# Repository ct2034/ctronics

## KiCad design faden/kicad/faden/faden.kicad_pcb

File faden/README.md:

Pedal properties
----------------

* based on  [General Guitar Gadgets](http://www.generalguitargadgets.com/how-to-build-it/technical-help/articles/design-distortion/) ([pdf](/faden/DesignYourOwnDistortion_GeneralGuitarGadgets.pdf))
* tweaks:
  * For low tunings (C2 - 65,4Hz lowest note) 
  * BigMuff-style tone control (see pdf)

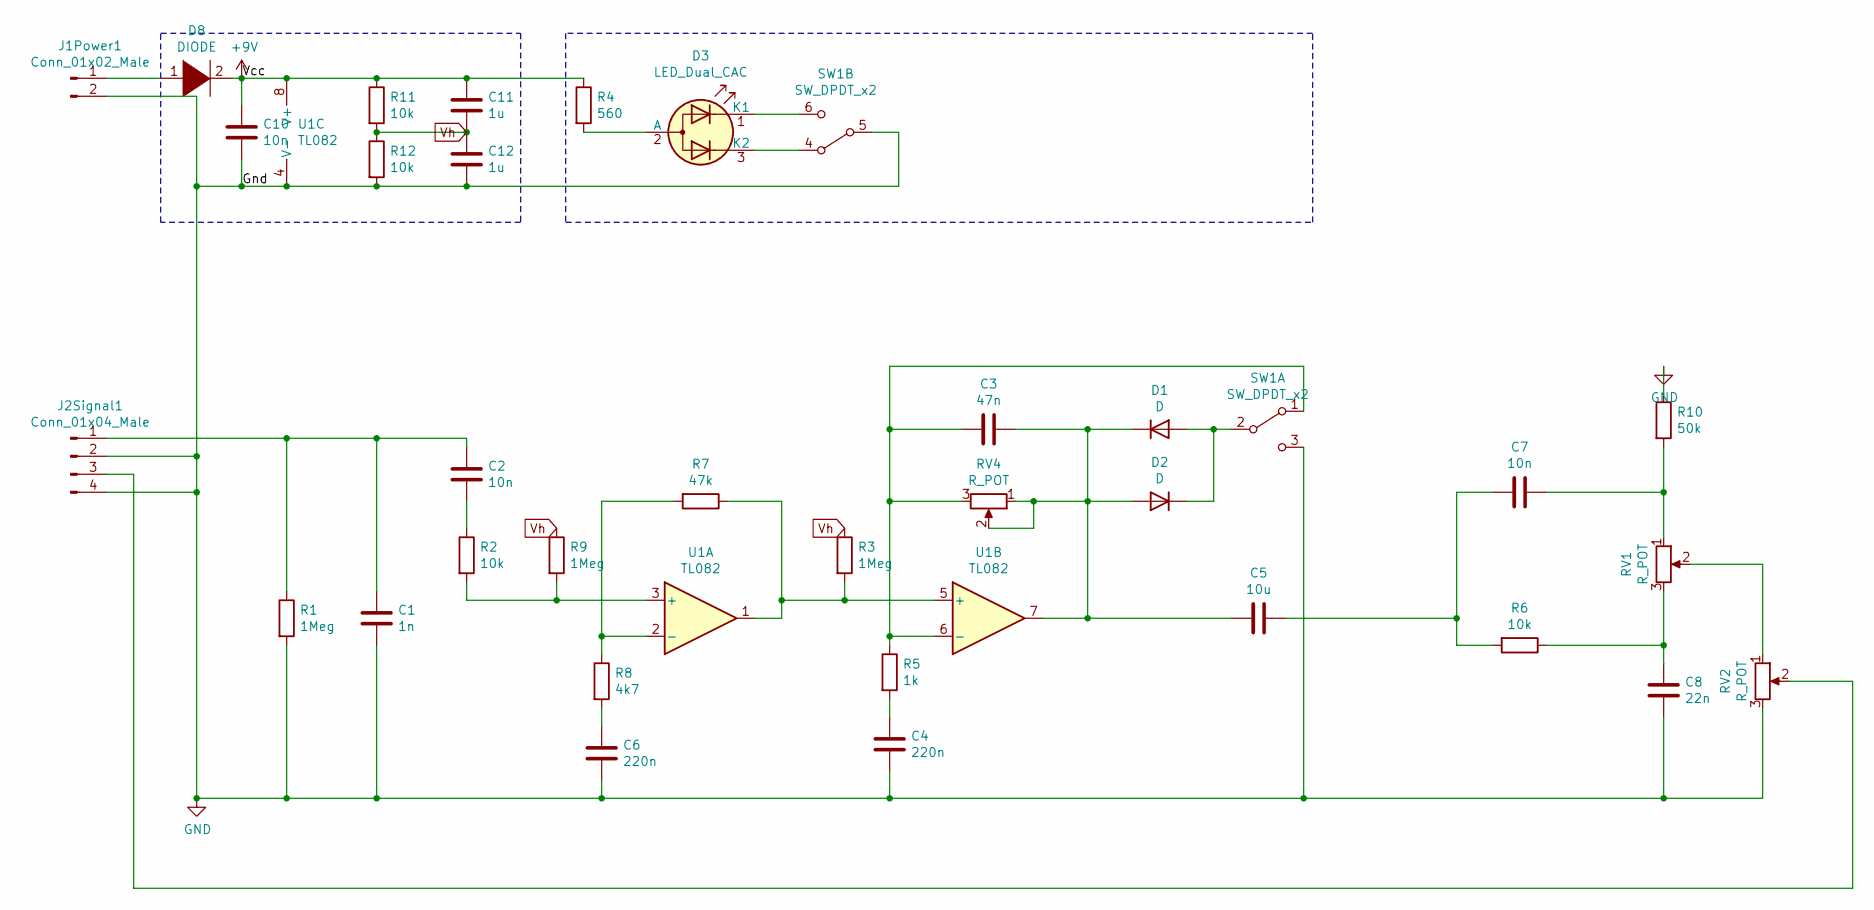
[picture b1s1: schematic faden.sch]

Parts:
C1: 1n; C_Disc_D5.0mm_W2.5mm_P2.50mm
C2: 10n; C_Disc_D5.0mm_W2.5mm_P5.00mm
C3: 47n; C_Disc_D3.0mm_W1.6mm_P2.50mm
C4, C6: 220n; C_Disc_D5.0mm_W2.5mm_P5.00mm
C5: 10u; CP_Radial_D5.0mm_P2.50mm
C7, C10: 10n; C_Disc_D4.3mm_W1.9mm_P5.00mm
C8: 22n; C_Disc_D4.3mm_W1.9mm_P5.00mm
C11, C12: 1u; CP_Radial_D5.0mm_P2.50mm
D1, D2: D; D_DO-34_SOD68_P7.62mm_Horizontal
D3: LED_Dual_CAC; LED_D3.0mm-3
D8: DIODE; D_DO-15_P10.16mm_Horizontal
J1Power1: Conn_01x02_Male; PinHeader_1x02_P2.54mm_Vertical
J2Signal1: Conn_01x04_Male; PinHeader_1x04_P2.54mm_Vertical
R1: 1Meg; R_Axial_DIN0207_L6.3mm_D2.5mm_P7.62mm_Horizontal
R2, R11, R12: 10k; R_Axial_DIN0207_L6.3mm_D2.5mm_P7.62mm_Horizontal
R3, R9: 1Meg; R_Axial_DIN0207_L6.3mm_D2.5mm_P10.16mm_Horizontal
R4: 560; R_Axial_DIN0207_L6.3mm_D2.5mm_P7.62mm_Horizontal
R5: 1k; R_Axial_DIN0207_L6.3mm_D2.5mm_P10.16mm_Horizontal
R6: 10k; R_Axial_DIN0207_L6.3mm_D2.5mm_P10.16mm_Horizontal
R7: 47k; R_Axial_DIN0207_L6.3mm_D2.5mm_P10.16mm_Horizontal
R8: 4k7; R_Axial_DIN0207_L6.3mm_D2.5mm_P10.16mm_Horizontal
R10: 50k; R_Axial_DIN0207_L6.3mm_D2.5mm_P10.16mm_Horizontal
RV1, RV2, RV4: R_POT; Potentiometer_Vishay_T73XW_Horizontal
SW1: SW_DPDT_x2; SW_E-Switch_EG1271_DPDT
U1: TL082; DIP-8_W7.62mm_Socket

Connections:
+9V: C10.1, C11.1, D8.2 (A), R4.1, R11.1, U1.8 (V+)
GND: C1.2, C4.2, C6.2, C8.2, C10.2, C12.2, J1Power1.2, J2Signal1.2, J2Signal1.4, R1.2, R10.1, R12.2, RV2.3, SW1.3 (C), SW1.5 (B), U1.4 (V-)
unnamed: C1.1, C2.1, J2Signal1.1, R1.1
unnamed: C2.2, R2.1
unnamed 4: C3.1, C5.2, D1.1 (K), D2.2 (A), RV4.1, RV4.2, U1.7; also elsewhere on the board
unnamed 5: C3.2, R5.1, RV4.3, SW1.1 (A), U1.6 (-); also elsewhere on the board
unnamed: C4.1, R5.2
unnamed: C5.1, C7.2, R6.2
unnamed: C6.1, R8.2
unnamed: C7.1, R10.2, RV1.1
unnamed: C8.1, R6.1, RV1.3
unnamed: D1.2 (A), D2.1 (K), SW1.2 (B)
unnamed: D3.1 (K1), SW1.6 (C)
unnamed: D3.2 (A), R4.2
unnamed: D3.3 (K2), SW1.4 (A)
unnamed: D8.1 (K), J1Power1.1
unnamed: J2Signal1.3, RV2.2
unnamed: R2.2, R9.2, U1.3 (+)
unnamed: R3.2, R7.1, U1.1, U1.5 (+)
unnamed: R7.2, R8.1, U1.2 (-)
unnamed: RV1.2, RV2.1
Vh: C11.2, C12.1, R3.1, R9.1, R11.2, R12.1

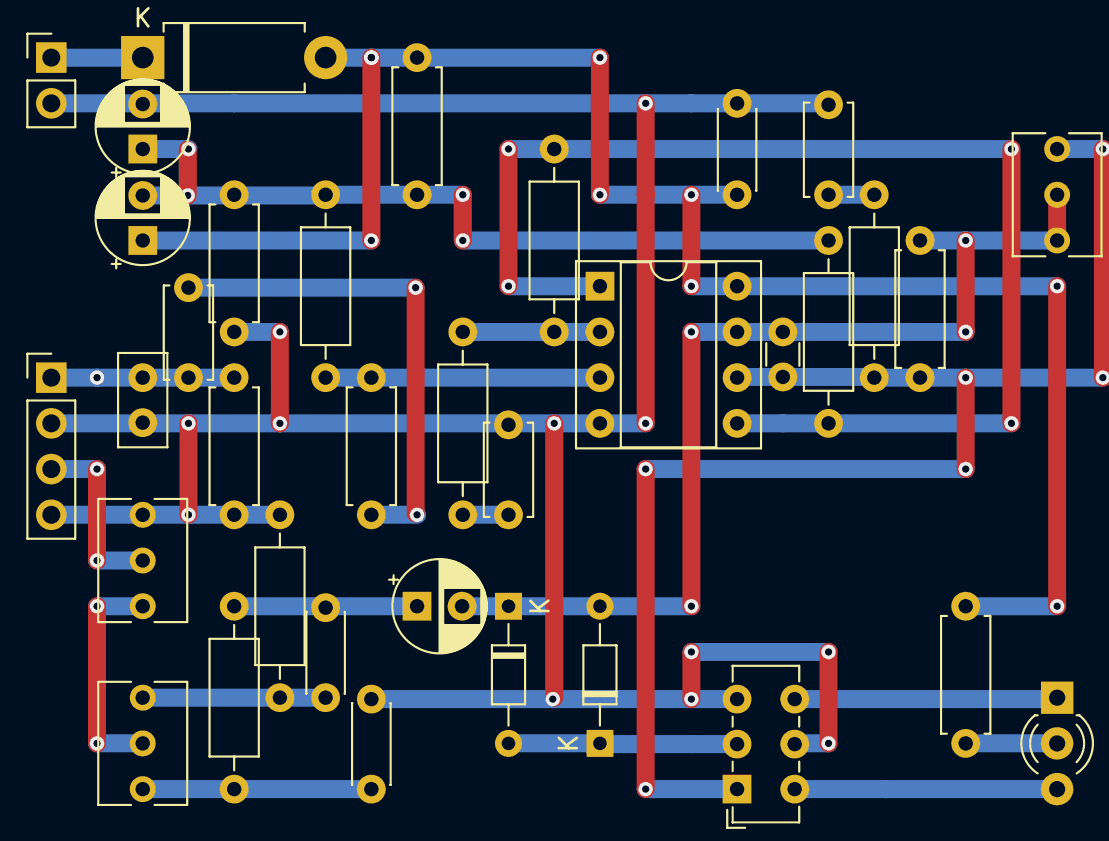
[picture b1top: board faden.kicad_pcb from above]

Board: 2 copper layers, 35 parts (0 on the bottom side), 22 nets.

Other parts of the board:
R4#2: 100k; R_Axial_DIN0207_L6.3mm_D2.5mm_P7.62mm_Horizontal

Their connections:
unnamed 4: R4#2.1; also elsewhere on the board
unnamed 5: R4#2.2; also elsewhere on the board

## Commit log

2020-08-30 start of a pedal
2020-09-01 simulation ltspice
2020-09-08 simulations of circuit
2020-09-08 a layout
2020-10-02 final layout for strip layout
